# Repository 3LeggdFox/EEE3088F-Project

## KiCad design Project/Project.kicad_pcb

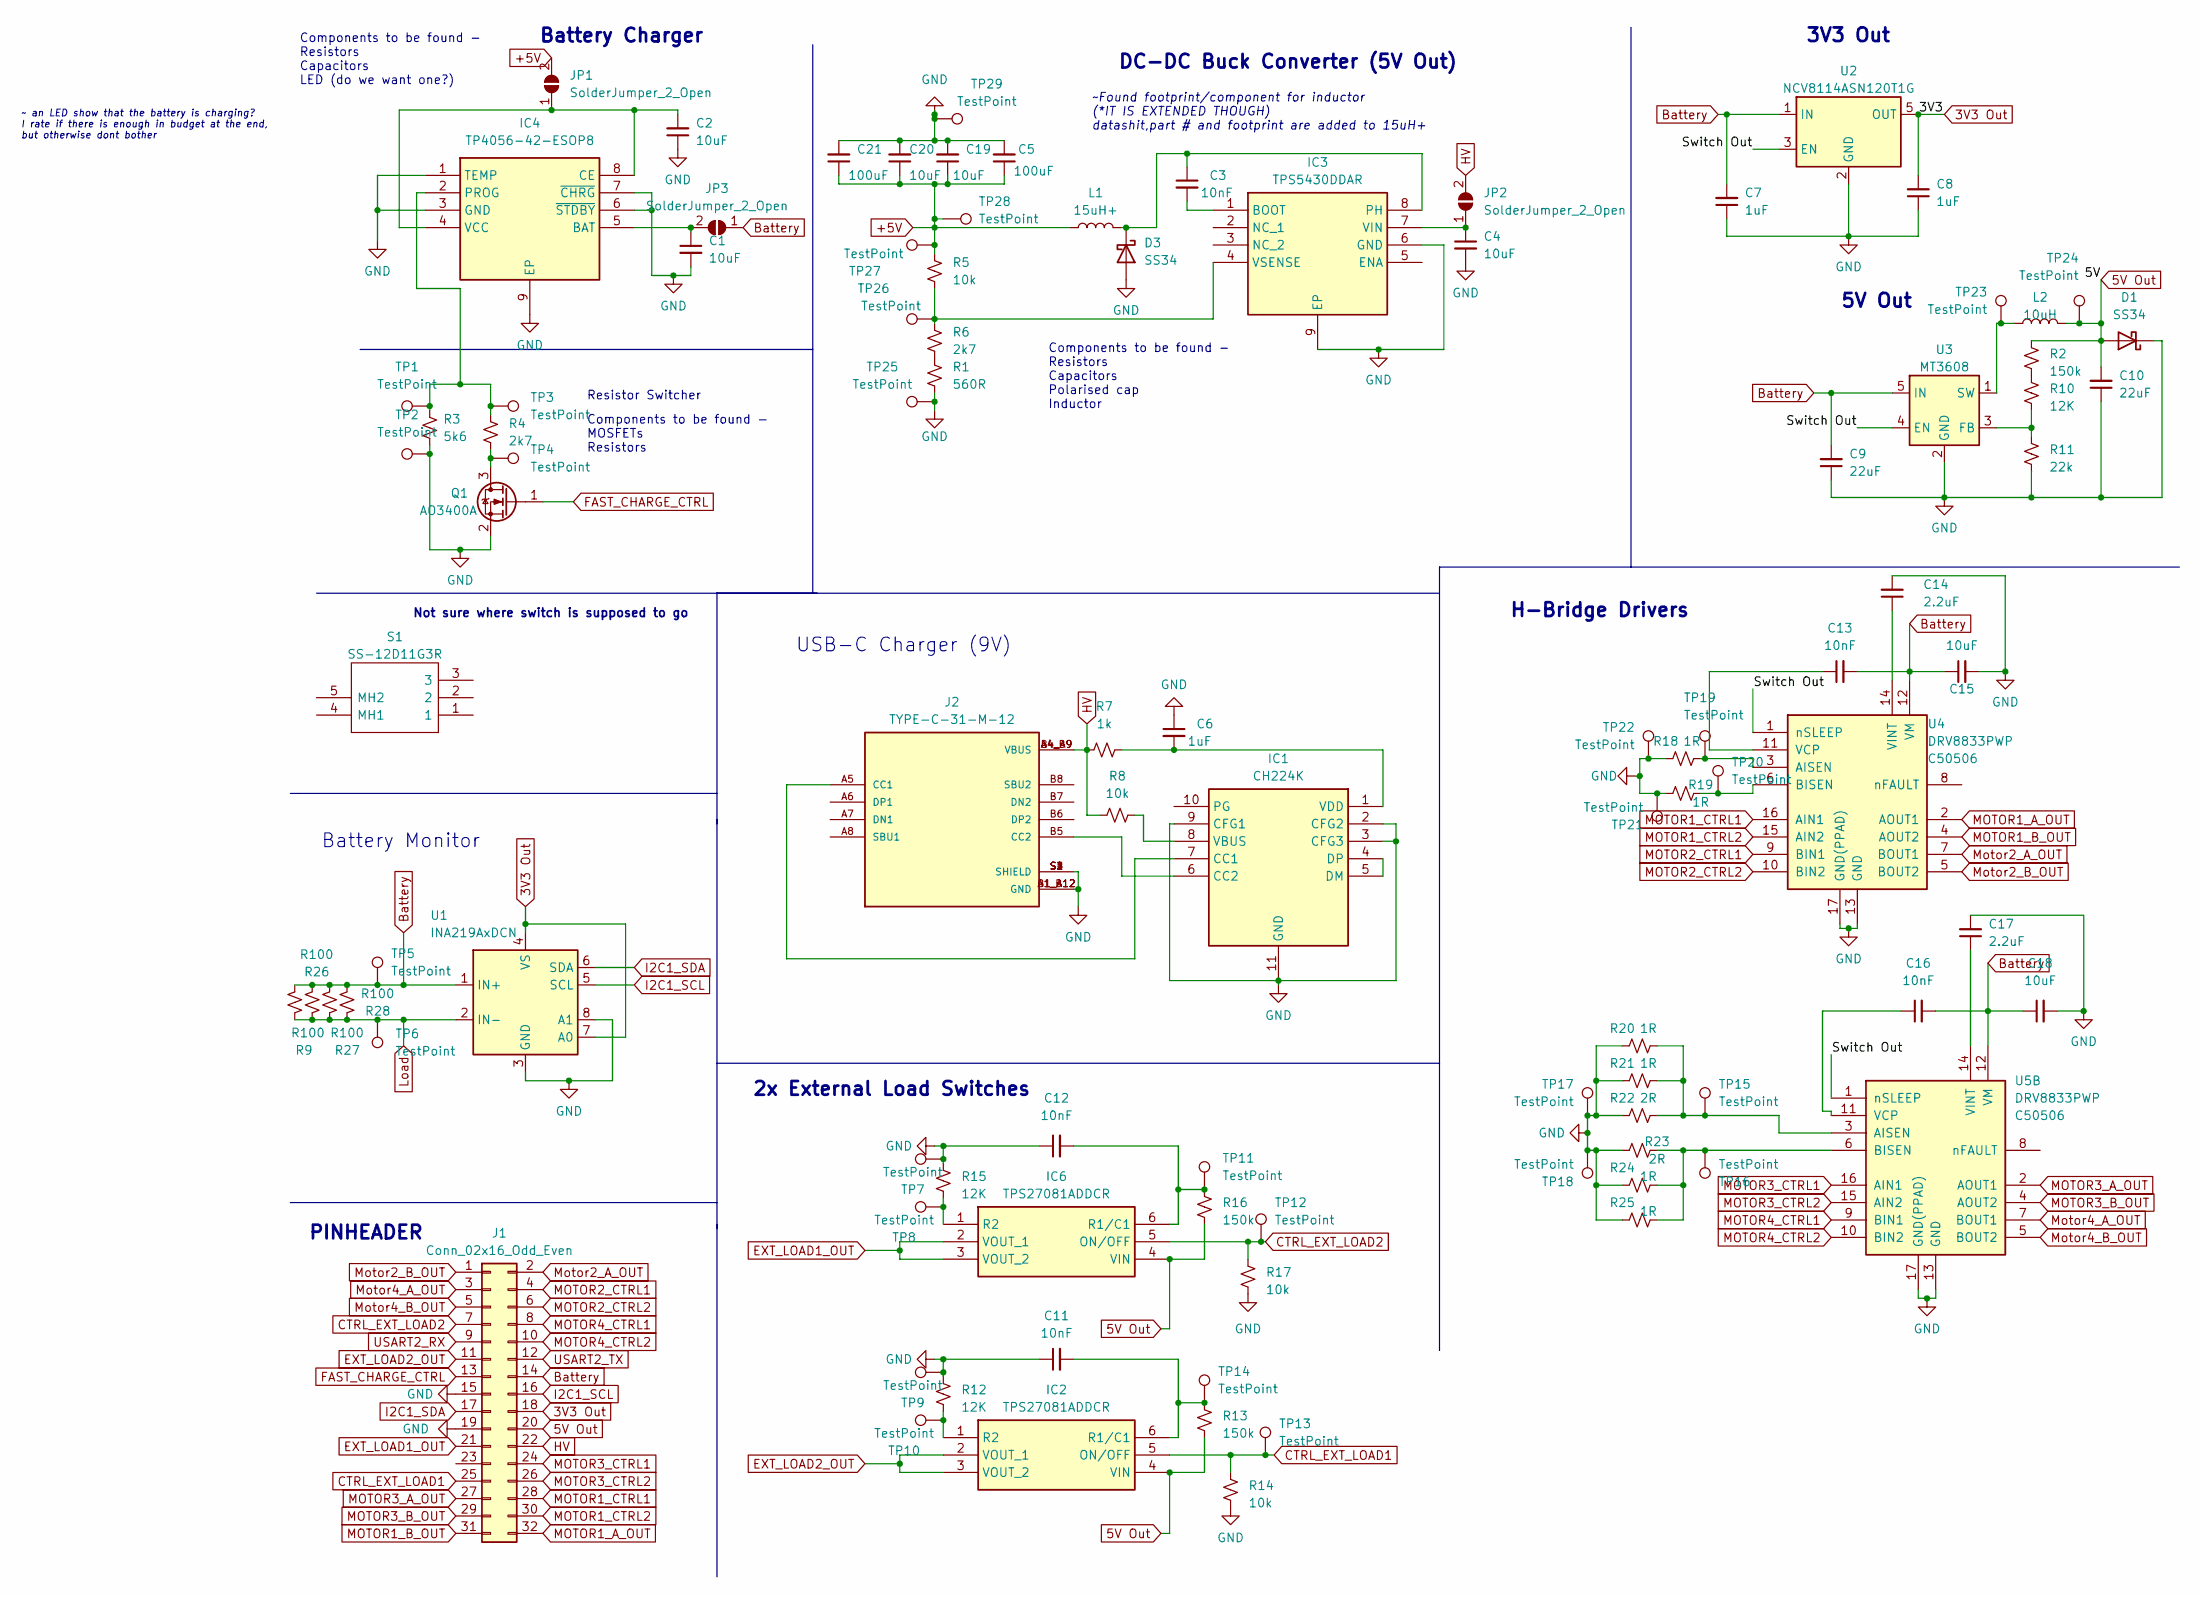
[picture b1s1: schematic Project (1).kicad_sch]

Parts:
C1: 10uF; R_0805_2012Metric; LCSC C19702
C2, C4, C15, C18, C19, C20: 10uF; C_0603_1608Metric; LCSC C19702
C3, C11, C12, C13, C16: 10nF; C_0402_1005Metric; LCSC C15195
C5, C21: 100uF; C_1206_3216Metric; LCSC C15008
C6, C7, C8: 1uF; C_0402_1005Metric; LCSC C52923
C9, C10: 22uF; C_0603_1608Metric; LCSC C59461
C14, C17: 2.2uF; C_0402_1005Metric; LCSC C12530
D1, D3: SS34; D_SMA
IC1: CH224K; SOP100P600X180-11N; Manufacturer_Part_Number CH224K
IC2, IC6: TPS27081ADDCR; SOT95P280X110-6N; Manufacturer_Part_Number TPS27081ADDCR; Mouser Part Number 595-TPS27081ADDCR
IC3: TPS5430DDAR; SOIC127P600X170-9N; Manufacturer_Part_Number TPS5430DDAR; Mouser Part Number 595-TPS5430DDAR
IC4: TP4056-42-ESOP8; SOIC127P600X175-9N; Manufacturer_Part_Number TP4056-42-ESOP8
J1: Conn_02x16_Odd_Even
J2: TYPE-C-31-M-12; HRO_TYPE-C-31-M-12; PARTREV 2020.12.08; LCSC C165948
JP1, JP2, JP3: SolderJumper_2_Open
L1: 15uH+; L_Sunlord_MWSA0603S; LCSC C167969C408452
L2: 10uH; L_0805_2012Metric; LCSC C1046
Q1: AO3400A; SOT-23; LCSC C20917
R1: 560R; R_0603_1608Metric; LCSC C23204
R2, R13, R16: 150k; R_0805_2012Metric; LCSC C17470
R3: 5k6; R_0805_2012Metric; LCSC C4382
R4, R6: 2k7; R_0603_1608Metric; LCSC C13167
R5, R8, R14, R17: 10k; R_0805_2012Metric; LCSC C17414
R7: 1k; R_1206_3216Metric; LCSC C4410
R9, R26, R27, R28: R100; R_1206_3216Metric; LCSC C25334
R10, R12, R15: 12K; R_0805_2012Metric; LCSC C17444
R11: 22k; R_0805_2012Metric; LCSC C17560
R18, R19, R20, R21, R24, R25: 1R; RESC1608X55N; LCSC C22936
R22, R23: 2R; RESC1608X55N; LCSC C22977
S1: SS-12D11G3R; SS12D11G3R; Manufacturer_Part_Number SS-12D11G3R; LCSC C843362
TP1, TP2, TP3, TP4, TP5, TP6, TP7, TP8, TP9, TP10, TP11, TP12, TP13, TP14, TP15, TP16, TP17, TP18, TP19, TP20, TP21, TP22, TP23, TP24, TP25, TP26, TP27, TP28, TP29: TestPoint
U1: INA219AxDCN; SOT-23-8
U2: NCV8114ASN120T1G; TSOT-23-5; LCSC C3021085
U3: MT3608; SOT-23-6; LCSC C84817
U4, U5: DRV8833PWP; HTSSOP-16-1EP_4.4x5mm_P0.65mm_EP3.4x5mm_Mask2.46x2.31mm_The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; LCSC C50506

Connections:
3V3 Out: C8.2, J1.18, U1.4 (VS), U1.7 (A0), U2.5 (OUT)
5V Out: C10.2, D1.2 (A), IC2.4 (VIN), IC6.4 (VIN), J1.20, L2.2, R2.1, R13.1, R16.1, TP24.1
+5V: C5.1, C19.1, C20.1, C21.1, JP1.2 (B), L1.1, R5.1, TP27.1, TP28.1
CTRL_EXT_LOAD1: IC2.5 (ON/OFF), J1.25, R14.1, TP13.1
CTRL_EXT_LOAD2: IC6.5 (ON/OFF), J1.7, R17.1, TP12.1
EXT_LOAD1_OUT: IC6.2 (VOUT_1), IC6.3 (VOUT_2), J1.21
EXT_LOAD2_OUT: IC2.2 (VOUT_1), IC2.3 (VOUT_2), J1.11
FAST_CHARGE_CTRL: J1.13, Q1.1 (G)
HV: J1.22, J2.A4_B9 (VBUS), J2.B4_A9 (VBUS), JP2.2 (B), R7.1, R8.1
I2C1_SCL: J1.16, U1.5 (SCL)
I2C1_SDA: J1.17, U1.6 (SDA)
MOTOR1_A_OUT: J1.32, U4.2 (AOUT1)
MOTOR1_B_OUT: J1.31, U4.4 (AOUT2)
MOTOR1_CTRL1: J1.28, U4.16 (AIN1)
MOTOR1_CTRL2: J1.30, U4.15 (AIN2)
MOTOR2_CTRL1: J1.4, U4.9 (BIN1)
MOTOR2_CTRL2: J1.6, U4.10 (BIN2)
MOTOR3_A_OUT: J1.27, U5.2 (AOUT1)
MOTOR3_B_OUT: J1.29, U5.4 (AOUT2)
MOTOR3_CTRL1: J1.24, U5.16 (AIN1)
MOTOR3_CTRL2: J1.26, U5.15 (AIN2)
MOTOR4_CTRL1: J1.8, U5.9 (BIN1)
MOTOR4_CTRL2: J1.10, U5.10 (BIN2)
Motor2_A_OUT: J1.2, U4.7 (BOUT1)
Motor2_B_OUT: J1.1, U4.5 (BOUT2)
Motor4_A_OUT: J1.3, U5.7 (BOUT1)
Motor4_B_OUT: J1.5, U5.5 (BOUT2)
unnamed: C3.1, D3.1 (K), IC3.8 (PH), L1.2
unnamed: IC1.7 (CC1), J2.A5 (CC1)
unnamed: IC1.6 (CC2), J2.B5 (CC2)
unnamed: IC1.4 (DP), IC1.5 (DM)
unnamed: IC1.8 (VBUS), R8.2
unnamed: C6.2, IC1.1 (VDD), R7.2
unnamed: C11.2, IC2.6 (R1/C1), R13.2, TP14.1
unnamed: IC2.1 (R2), R12.2, TP10.1
unnamed: C3.2, IC3.1 (BOOT)
unnamed: C4.1, IC3.7 (VIN), JP2.1 (A)
unnamed: IC3.4 (VSENSE), R5.2, R6.1, TP26.1
unnamed: C1.1, IC4.5 (BAT), JP3.2 (B)
unnamed: C2.2, IC4.4 (VCC), IC4.8 (CE), JP1.1 (A)
unnamed: IC4.2 (PROG), R3.1, R4.1, TP1.1, TP3.1
unnamed: C12.2, IC6.6 (R1/C1), R16.2, TP11.1
unnamed: IC6.1 (R2), R15.2, TP8.1
unnamed: Q1.3 (D), R4.2, TP4.1
unnamed: R1.1, R6.2
unnamed: R2.2, R10.1
unnamed: R10.2, R11.1, U3.3 (FB)
unnamed: L2.1, TP23.1, U3.1 (SW)
unnamed: R18.2, TP19.1, U4.3 (AISEN)
unnamed: R19.2, TP20.1, U4.6 (BISEN)
unnamed: C13.1, U4.11 (VCP)
unnamed: C14.1, U4.14 (VINT)
unnamed: R20.2, R21.2, R22.2, TP15.1, U5.3 (AISEN)
unnamed: R23.2, R24.2, R25.2, TP16.1, U5.6 (BISEN)
unnamed: C16.1, U5.11 (VCP)
unnamed: C17.1, U5.14 (VINT)
USART2_RX: J1.9
USART2_TX: J1.12

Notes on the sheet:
H-Bridge Drivers
~Found footprint/component for inductor (*IT IS EXTENDED THOUGH) datashit,part # and footprint are added to 15uH+
USB-C Charger (9V)
5V Out
Resistor Switcher
DC-DC Buck Converter (5V Out)
Components to be found - MOSFETs Resistors
2x External Load Switches
Battery Charger
Not sure where switch is supposed to go
Components to be found - Resistors Capacitors LED (do we want one?)
Battery Monitor
~ an LED show that the battery is charging? I rate if there is enough in budget at the end, but otherwise dont bother
Components to be found - Resistors Capacitors Polarised cap Inductor
3V3 Out
PINHEADER

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
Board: 2 copper layers, 101 parts (0 on the bottom side), 62 nets, no tracks yet.

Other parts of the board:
FB1: FerriteBead; BEADC1608X95N
J3: Conn_01x02; JST_PH_S2B-PH-K_1x02_P2.00mm_Horizontal

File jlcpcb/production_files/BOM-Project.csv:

Comment,Designator,Footprint,LCSC,Quantity
FerriteBead,FB1,BEADC1608X95N,C1002,1
10uH,L2,L_0805_2012Metric,C1046,1
2.2uF,"C14,C17",C_0402_1005Metric,C12530,2
TPS27081ADDCR,"IC2,IC6",SOT95P280X110-6N,C128404,2
2k7,"R4,R6",R_0603_1608Metric,C13167,2
100uF,"C21,C5",C_1206_3216Metric,C15008,2
10nF,"C11,C12,C13,C16,C3",C_0402_1005Metric,C15195,5
TP4056-42-ESOP8,IC4,SOIC127P600X175-9N,C16581,1
TYPE-C-31-M-12,J2,HRO_TYPE-C-31-M-12,C165948,1
10k,"R14,R17,R5,R8",R_0805_2012Metric,C17414,4
12K,"R10,R12,R15",R_0805_2012Metric,C17444,3
150k,"R13,R16,R2",R_0805_2012Metric,C17470,3
22k,R11,R_0805_2012Metric,C17560,1
10uF,"C1,C15,C18,C19,C2,C20,C4",C_0603_1608Metric,C19702,7
AO3400A,Q1,SOT-23,C20917,1
1R,"R18,R19,R20,R21,R24,R25",R_0603_1608Metric,C22936,6
2R,"R22,R23",R_0603_1608Metric,C22977,2
560R,R1,R_0603_1608Metric,C23204,1
R100,"R26,R27,R28,R9",R_1206_3216Metric,C25334,4
TPAP2112K-3.3TRG1,IC5,SOT95P280X125-5N,C3021085,1
5k6,R3,R_0805_2012Metric,C4382,1
1k,R7,R_1206_3216Metric,C4410,1
DRV8833PWP,"U4,U5",HTSSOP-16-1EP_4.4x5mm_P0.65mm_EP3.4x5mm_Mask2.46x2.31mm_ThermalVias,C50506,2
1uF,"C6,C7,C8",C_0402_1005Metric,C52923,3
22uF,"C10,C9",C_0603_1608Metric,C59461,2
SS-12D11G3R,S1,SS12D11G3R,C843362,1
MT3608,U3,SOT-23-6,C84817,1
SS34,"D1,D3",D_SMA,C8678,2
INA219AxDCN,U1,SOT-23-8,C87469,1
CH224K,IC1,SOP100P600X180-11N,C970725,1
TPS5430DDAR,IC3,SOIC127P600X170-9N,C9864,1
15uH,L1,L_Sunlord_MWSA0603S,C408452,1

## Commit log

2025-03-26 Add files via upload
    - added footprints for resistors and inductor
    - made more space
2025-03-28 Submission Files
